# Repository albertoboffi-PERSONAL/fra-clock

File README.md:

# fra-clock

A one-off gift PCB designed in **KiCad 10**: an ESP32 clock with a ring of 180 WS2812B‑2020 LEDs, a photo printed in exposed copper on the front, two Makerverse 8 Ω / 5 W speakers driven by two MAX98357A I²S amplifiers, USB‑C power/programming (CH340C) and an NFC tag area.

| | |
|---|---|
| Board | 2 layers, 210 × 297 mm (A4), R3 corners |
| MCU | ESP32‑WROOM‑32E |
| LEDs | 180 × WS2812B‑2020 (4 chains, 74AHCT125 level shifter) |
| Audio | 2 × MAX98357A → 2 × JST PH (speakers Core Electronics CE08483) |
| Power / USB | USB‑C (HRO TYPE‑C‑31‑M‑12), 2 A PTC, AP2112K‑3.3, USBLC6‑2SC6, CH340C |
| Status | Routed, DRC clean (0 errors, 0 unconnected), Gerber/drill + JLCPCB BOM/CPL generated. **Not fabricated yet.** |

## Repository layout

```
hardware/                 KiCad project – open hardware/fra_clock.kicad_pro
  fra_clock.kicad_pcb     board
  fra_clock.kicad_sch     root schematic (+ led_ring.kicad_sch sub-sheet)
  fra_clock.pretty/       project footprints (photo art ART_FOTO, speaker outline)
  3d/                     project 3D models (speaker, LCSC/EasyEDA models in lcsc/)
production/
  fra_clock_gerber_jlcpcb.zip   upload this to the fab
  gerber/                 Gerber X2 + Excellon drill (+ drill maps)
  assembly/               JLCPCB BOM and CPL (pick & place)
  preview/                Gerber renders used for the visual check
docs/
  routing-report.md       full design/routing report (Italian)
  checks/                 DRC and verification outputs referenced by the report
  images/                 3D renders
art/
  source/foto.jpeg        original photo
  generated/              dithered bitmap, rectangle list, previews
scripts/                  automation used to build the board (see scripts/README.md)
```

## Ordering (JLCPCB)

1. Upload `production/fra_clock_gerber_jlcpcb.zip` (2 layers, 1.6 mm).
2. Surface finish: **ENIG** keeps the copper photo gold and flat (HASL turns it silver and uneven). Solder-mask colour sets the photo contrast.
3. For assembly upload `production/assembly/fra_clock_BOM_JLCPCB.csv` and `fra_clock_CPL_JLCPCB.csv`, then check rotation / pin 1 in the placement preview (SOT‑23/‑5/‑6, SOIC, TQFN, WS2812B‑2020, ESP32 antenna towards the edge, USB‑C, JST, C69 polarity).
4. Open decisions before ordering: ESP32 flash size (BOM uses N4 = C701341; N8 = C701342, N16 = C701343); stock and prices were not checked.

The NFC tag (NTAG216 sticker) has no footprint and is applied by hand in the keep-out area.

## Regenerating the production files

From the repository root, with KiCad 10 (`kicad-cli`):

```sh
KC=/Applications/KiCad/KiCad.app/Contents/MacOS/kicad-cli
$KC pcb drc --refill-zones --schematic-parity --format json --severity-all -o docs/checks/drc_latest.json hardware/fra_clock.kicad_pcb
$KC pcb export gerbers -o production/gerber/ --layers F.Cu,B.Cu,F.Paste,B.Paste,F.Silkscreen,B.Silkscreen,F.Mask,B.Mask,Edge.Cuts --subtract-soldermask --check-zones hardware/fra_clock.kicad_pcb
$KC pcb export drill -o production/gerber/ --format excellon --drill-origin absolute --excellon-units mm --excellon-zeros-format decimal --excellon-oval-format alternate --excellon-separate-th --generate-map --map-format gerberx2 hardware/fra_clock.kicad_pcb
python3 scripts/production/dump_fps.py hardware/fra_clock.kicad_pcb /tmp/fps.json
(cd production/assembly && python3 ../../scripts/production/make_bom_cpl.py /tmp/fps.json)
```

## Known open points

See `docs/routing-report.md` §5: a ~1035 mm² island of the bottom GND pour around U6/C4 is tied to GND only through top-side bridges; the exposed-pad vias of U101/U102 are not plugged; the `Power` net class is not assigned (widths are set explicitly on the tracks).

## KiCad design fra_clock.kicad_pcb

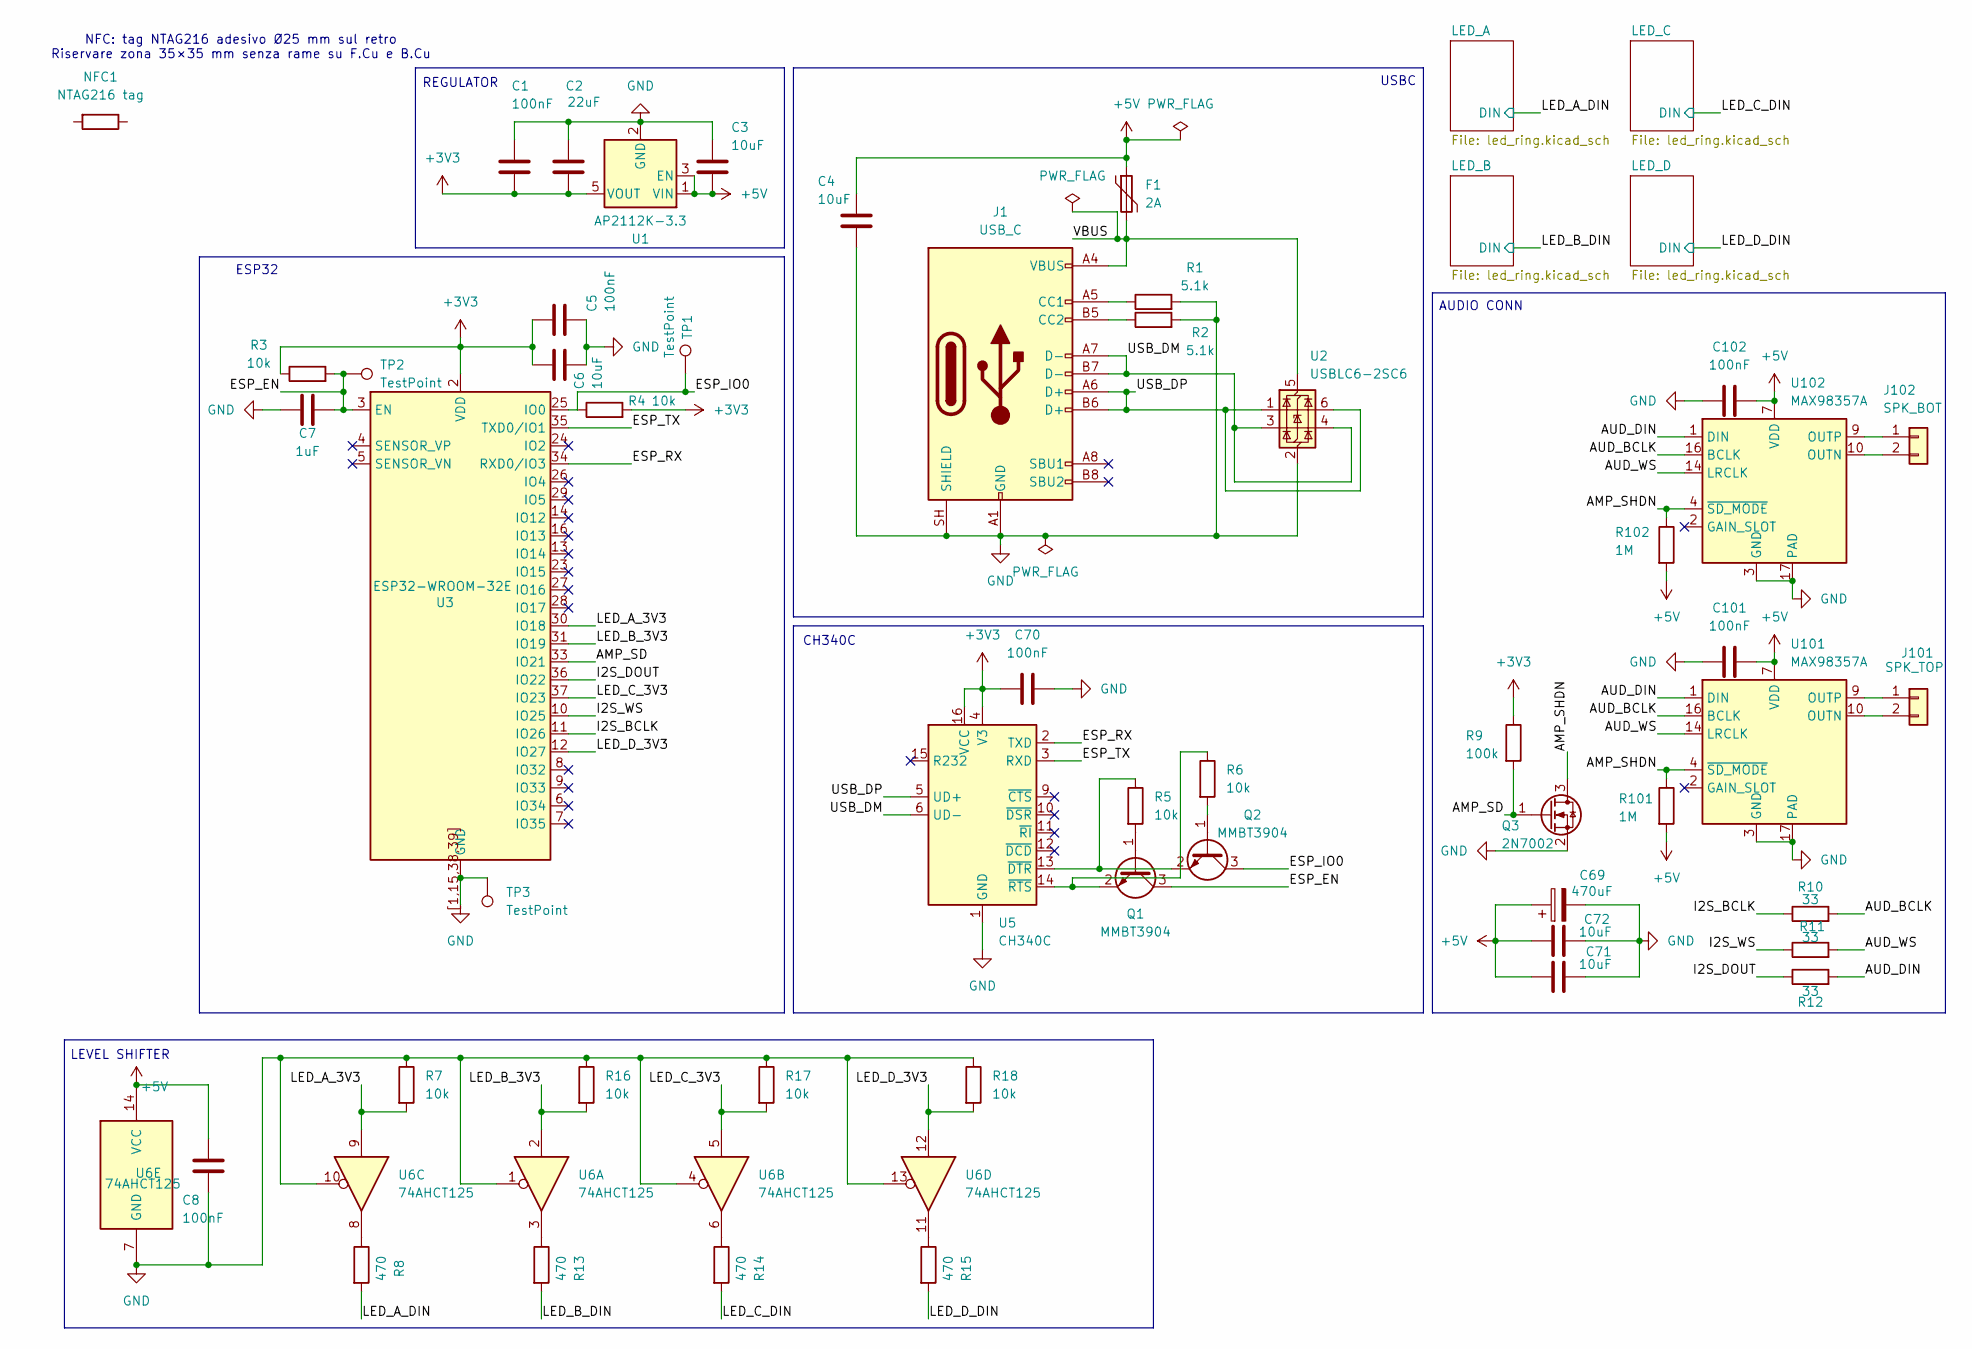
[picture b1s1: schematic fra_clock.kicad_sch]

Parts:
C1, C5, C8, C70: 100nF; C_0603_1608Metric
C2: 22uF; C_0805_2012Metric
C3, C4, C6, C71, C72: 10uF; C_0805_2012Metric
C7: 1uF; C_0603_1608Metric
C69: 470uF; CP_Elec_8x10
C101, C102: 100nF; C_0402_1005Metric
F1: 2A; Fuse_1812_4532Metric
J1: USB_C; USB_C_Receptacle_HRO_TYPE-C-31-M-12
J101: SPK_TOP; JST_PH_S2B-PH-SM4-TB_1x02-1MP_P2.00mm_Horizontal
J102: SPK_BOT; JST_PH_S2B-PH-SM4-TB_1x02-1MP_P2.00mm_Horizontal
NFC1: NTAG216 tag
Q1, Q2: MMBT3904; SOT-23
Q3: 2N7002; SOT-23
R1, R2: 5.1k; R_0603_1608Metric
R3, R4, R5, R6, R7, R16, R17, R18: 10k; R_0603_1608Metric
R8, R13, R14, R15: 470; R_0603_1608Metric
R9: 100k; R_0603_1608Metric
R10, R11, R12: 33; R_0603_1608Metric
R101, R102: 1M; R_0603_1608Metric
TP1, TP2, TP3: TestPoint; TestPoint_Pad_D1.5mm
U1: AP2112K-3.3; SOT-23-5
U2: USBLC6-2SC6; SOT-23-6
U3: ESP32-WROOM-32E
U5: CH340C; SOIC-16_3.9x9.9mm_P1.27mm
U6: 74AHCT125; SOIC-14_3.9x8.7mm_P1.27mm
U101, U102: MAX98357A; TQFN-16-1EP_3x3mm_P0.5mm_EP1.23x1.23mm

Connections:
+3V3: C1.2, C2.2, C5.1, C6.1, C70.1, R3.1, R4.2, R9.1, U1.5 (VOUT), U3.2 (VDD), U5.4 (V3), U5.16 (VCC)
+5V: C3.2, C4.1, C8.1, C69.1, C71.1, C72.1, C101.1, C102.1, F1.1, R101.2, R102.2, U1.1 (VIN), U1.3 (EN), U6.14 (VCC), U101.7 (VDD), U101.8 (VDD), U102.7 (VDD), U102.8 (VDD); also elsewhere on the board
/AMP_SD: Q3.1 (G), R9.2, U3.33 (IO21)
/AMP_SHDN: Q3.3 (D), R101.1, R102.1, U101.4 (~SD_MODE), U102.4 (~SD_MODE)
/AUD_BCLK: R10.2, U101.16 (BCLK), U102.16 (BCLK)
/AUD_DIN: R12.2, U101.1 (DIN), U102.1 (DIN)
/AUD_WS: R11.2, U101.14 (LRCLK), U102.14 (LRCLK)
/ESP_EN: C7.1, Q1.3 (C), R3.2, TP2.1 (1_1), U3.3 (EN)
/ESP_IO0: Q2.3 (C), R4.1, TP1.1 (1_1), U3.25 (IO0)
/ESP_RX: U3.34 (RXD0/IO3), U5.2 (TXD)
/ESP_TX: U3.35 (TXD0/IO1), U5.3 (RXD)
/I2S_BCLK: R10.1, U3.11 (IO26)
/I2S_DOUT: R12.1, U3.36 (IO22)
/I2S_WS: R11.1, U3.10 (IO25)
/LED_A_3V3: R7.2, U3.30 (IO18), U6.9
/LED_A_DIN: R8.2; also elsewhere on the board
/LED_B_3V3: R16.2, U3.31 (IO19), U6.2
/LED_B_DIN: R13.2; also elsewhere on the board
/LED_C_3V3: R17.2, U3.37 (IO23), U6.5
/LED_C_DIN: R14.2; also elsewhere on the board
/LED_D_3V3: R18.2, U3.12 (IO27), U6.12
/LED_D_DIN: R15.2; also elsewhere on the board
/USB_DM: J1.A7 (D-), J1.B7 (D-), U2.3 (I/O2), U2.4 (I/O2), U5.6 (UD-)
/USB_DP: J1.A6 (D+), J1.B6 (D+), U2.1 (I/O1), U2.6 (I/O1), U5.5 (UD+)
/VBUS: F1.2, J1.A4 (VBUS), J1.A9 (VBUS), J1.B4 (VBUS), J1.B9 (VBUS), U2.5 (VBUS)
GND: C1.1, C2.1, C3.1, C4.2, C5.2, C6.2, C7.2, C8.2, C69.2, C70.2, C71.2, C72.2, C101.2, C102.2, J1.A1 (GND), J1.A12 (GND), J1.B1 (GND), J1.B12 (GND), J1.SH (SHIELD), Q3.2 (S), R1.2, R2.2, R7.1, R16.1, R17.1, R18.1, TP3.1 (1_1), U1.2 (GND), U2.2 (GND), U3.1 (GND), U3.15 (GND), U3.38 (GND), U3.39 (GND), U3.[1,15,38,39] (GND), U5.1 (GND), U6.1, U6.4, U6.7 (GND), U6.10, U6.13, U101.3 (GND), U101.11 (GND), U101.15 (GND), U101.17 (PAD), U102.3 (GND), U102.11 (GND), U102.15 (GND), U102.17 (PAD); also elsewhere on the board
unnamed: J1.A5 (CC1), R1.1
unnamed: J1.B5 (CC2), R2.1
unnamed: J101.1, U101.9 (OUTP)
unnamed: J101.2, U101.10 (OUTN)
unnamed: J102.1, U102.9 (OUTP)
unnamed: J102.2, U102.10 (OUTN)
unnamed: Q1.1 (B), R5.2
unnamed: Q1.2 (E), R6.1, U5.14 (~RTS)
unnamed: Q2.1 (B), R6.2
unnamed: Q2.2 (E), R5.1, U5.13 (~DTR)
unnamed: R8.1, U6.8
unnamed: R13.1, U6.3
unnamed: R14.1, U6.6
unnamed: R15.1, U6.11

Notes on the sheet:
CH340C
USBC
LEVEL SHIFTER
NFC: tag NTAG216 adesivo Ø25 mm sul retro Riservare zona 35×35 mm senza rame su F.Cu e B.Cu
AUDIO CONN
REGULATOR
ESP32

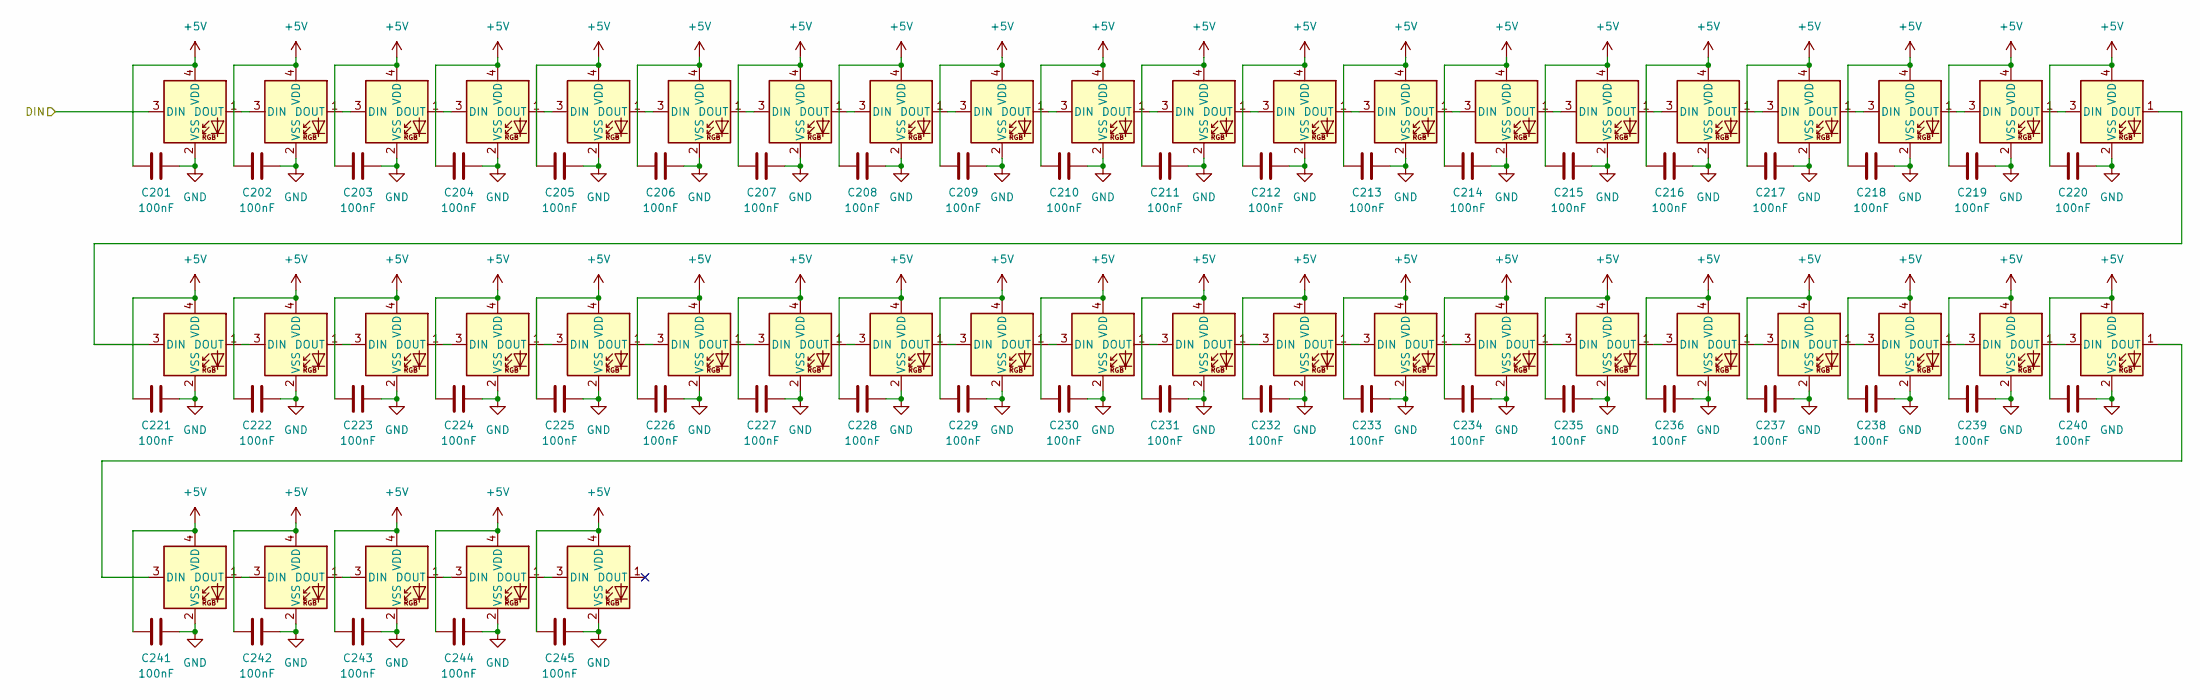
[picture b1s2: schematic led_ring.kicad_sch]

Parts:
C201, C202, C203, C204, C205, C206, C207, C208, C209, C210, C211, C212, C213, C214, C215, C216, C217, C218, C219, C220, C221, C222, C223, C224, C225, C226, C227, C228, C229, C230, C231, C232, C233, C234, C235, C236, C237, C238, C239, C240, C241, C242, C243, C244, C245: 100nF; C_0402_1005Metric
D201, D202, D203, D204, D205, D206, D207, D208, D209, D210, D211, D212, D213, D214, D215, D216, D217, D218, D219, D220, D221, D222, D223, D224, D225, D226, D227, D228, D229, D230, D231, D232, D233, D234, D235, D236, D237, D238, D239, D240, D241, D242, D243, D244, D245: WS2812B-2020; LED_WS2812B-2020_PLCC4_2.0x2.0mm

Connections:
+5V: C201.2, C202.2, C203.2, C204.2, C205.2, C206.2, C207.2, C208.2, C209.2, C210.2, C211.2, C212.2, C213.2, C214.2, C215.2, C216.2, C217.2, C218.2, C219.2, C220.2, C221.2, C222.2, C223.2, C224.2, C225.2, C226.2, C227.2, C228.2, C229.2, C230.2, C231.2, C232.2, C233.2, C234.2, C235.2, C236.2, C237.2, C238.2, C239.2, C240.2, C241.2, C242.2, C243.2, C244.2, C245.2, D201.4 (VDD), D202.4 (VDD), D203.4 (VDD), D204.4 (VDD), D205.4 (VDD), D206.4 (VDD), D207.4 (VDD), D208.4 (VDD), D209.4 (VDD), D210.4 (VDD), D211.4 (VDD), D212.4 (VDD), D213.4 (VDD), D214.4 (VDD), D215.4 (VDD), D216.4 (VDD), D217.4 (VDD), D218.4 (VDD), D219.4 (VDD), D220.4 (VDD), D221.4 (VDD), D222.4 (VDD), D223.4 (VDD), D224.4 (VDD), D225.4 (VDD), D226.4 (VDD), D227.4 (VDD), D228.4 (VDD), D229.4 (VDD), D230.4 (VDD), D231.4 (VDD), D232.4 (VDD), D233.4 (VDD), D234.4 (VDD), D235.4 (VDD), D236.4 (VDD), D237.4 (VDD), D238.4 (VDD), D239.4 (VDD), D240.4 (VDD), D241.4 (VDD), D242.4 (VDD), D243.4 (VDD), D244.4 (VDD), D245.4 (VDD); also elsewhere on the board
/LED_A_DIN: D201.3 (DIN); also elsewhere on the board
GND: C201.1, C202.1, C203.1, C204.1, C205.1, C206.1, C207.1, C208.1, C209.1, C210.1, C211.1, C212.1, C213.1, C214.1, C215.1, C216.1, C217.1, C218.1, C219.1, C220.1, C221.1, C222.1, C223.1, C224.1, C225.1, C226.1, C227.1, C228.1, C229.1, C230.1, C231.1, C232.1, C233.1, C234.1, C235.1, C236.1, C237.1, C238.1, C239.1, C240.1, C241.1, C242.1, C243.1, C244.1, C245.1, D201.2 (VSS), D202.2 (VSS), D203.2 (VSS), D204.2 (VSS), D205.2 (VSS), D206.2 (VSS), D207.2 (VSS), D208.2 (VSS), D209.2 (VSS), D210.2 (VSS), D211.2 (VSS), D212.2 (VSS), D213.2 (VSS), D214.2 (VSS), D215.2 (VSS), D216.2 (VSS), D217.2 (VSS), D218.2 (VSS), D219.2 (VSS), D220.2 (VSS), D221.2 (VSS), D222.2 (VSS), D223.2 (VSS), D224.2 (VSS), D225.2 (VSS), D226.2 (VSS), D227.2 (VSS), D228.2 (VSS), D229.2 (VSS), D230.2 (VSS), D231.2 (VSS), D232.2 (VSS), D233.2 (VSS), D234.2 (VSS), D235.2 (VSS), D236.2 (VSS), D237.2 (VSS), D238.2 (VSS), D239.2 (VSS), D240.2 (VSS), D241.2 (VSS), D242.2 (VSS), D243.2 (VSS), D244.2 (VSS), D245.2 (VSS); also elsewhere on the board
unnamed: D201.1 (DOUT), D202.3 (DIN)
unnamed: D202.1 (DOUT), D203.3 (DIN)
unnamed: D203.1 (DOUT), D204.3 (DIN)
unnamed: D204.1 (DOUT), D205.3 (DIN)
unnamed: D205.1 (DOUT), D206.3 (DIN)
unnamed: D206.1 (DOUT), D207.3 (DIN)
unnamed: D207.1 (DOUT), D208.3 (DIN)
unnamed: D208.1 (DOUT), D209.3 (DIN)
unnamed: D209.1 (DOUT), D210.3 (DIN)
unnamed: D210.1 (DOUT), D211.3 (DIN)
unnamed: D211.1 (DOUT), D212.3 (DIN)
unnamed: D212.1 (DOUT), D213.3 (DIN)
unnamed: D213.1 (DOUT), D214.3 (DIN)
unnamed: D214.1 (DOUT), D215.3 (DIN)
unnamed: D215.1 (DOUT), D216.3 (DIN)
unnamed: D216.1 (DOUT), D217.3 (DIN)
unnamed: D217.1 (DOUT), D218.3 (DIN)
unnamed: D218.1 (DOUT), D219.3 (DIN)
unnamed: D219.1 (DOUT), D220.3 (DIN)
unnamed: D220.1 (DOUT), D221.3 (DIN)
unnamed: D221.1 (DOUT), D222.3 (DIN)
unnamed: D222.1 (DOUT), D223.3 (DIN)
unnamed: D223.1 (DOUT), D224.3 (DIN)
unnamed: D224.1 (DOUT), D225.3 (DIN)
unnamed: D225.1 (DOUT), D226.3 (DIN)
unnamed: D226.1 (DOUT), D227.3 (DIN)
unnamed: D227.1 (DOUT), D228.3 (DIN)
unnamed: D228.1 (DOUT), D229.3 (DIN)
unnamed: D229.1 (DOUT), D230.3 (DIN)
unnamed: D230.1 (DOUT), D231.3 (DIN)
unnamed: D231.1 (DOUT), D232.3 (DIN)
unnamed: D232.1 (DOUT), D233.3 (DIN)
unnamed: D233.1 (DOUT), D234.3 (DIN)
unnamed: D234.1 (DOUT), D235.3 (DIN)
unnamed: D235.1 (DOUT), D236.3 (DIN)
unnamed: D236.1 (DOUT), D237.3 (DIN)
unnamed: D237.1 (DOUT), D238.3 (DIN)
unnamed: D238.1 (DOUT), D239.3 (DIN)
unnamed: D239.1 (DOUT), D240.3 (DIN)
unnamed: D240.1 (DOUT), D241.3 (DIN)
unnamed: D241.1 (DOUT), D242.3 (DIN)
unnamed: D242.1 (DOUT), D243.3 (DIN)
unnamed: D243.1 (DOUT), D244.3 (DIN)
unnamed: D244.1 (DOUT), D245.3 (DIN)

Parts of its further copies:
C301, C302, C303, C304, C305, C306, C307, C308, C309, C310, C311, C312, C313, C314, C315, C316, C317, C318, C319, C320, C321, C322, C323, C324, C325, C326, C327, C328, C329, C330, C331, C332, C333, C334, C335, C336, C337, C338, C339, C340, C341, C342, C343, C344, C345, C401, C402, C403, C404, C405, C406, C407, C408, C409, C410, C411, C412, C413, C414, C415, C416, C417, C418, C419, C420, C421, C422, C423, C424, C425, C426, C427, C428, C429, C430, C431, C432, C433, C434, C435, C436, C437, C438, C439, C440, C441, C442, C443, C444, C445, C501, C502, C503, C504, C505, C506, C507, C508, C509, C510, C511, C512, C513, C514, C515, C516, C517, C518, C519, C520, C521, C522, C523, C524, C525, C526, C527, C528, C529, C530, C531, C532, C533, C534, C535, C536, C537, C538, C539, C540, C541, C542, C543, C544, C545: 100nF; C_0402_1005Metric
D301, D302, D303, D304, D305, D306, D307, D308, D309, D310, D311, D312, D313, D314, D315, D316, D317, D318, D319, D320, D321, D322, D323, D324, D325, D326, D327, D328, D329, D330, D331, D332, D333, D334, D335, D336, D337, D338, D339, D340, D341, D342, D343, D344, D345, D401, D402, D403, D404, D405, D406, D407, D408, D409, D410, D411, D412, D413, D414, D415, D416, D417, D418, D419, D420, D421, D422, D423, D424, D425, D426, D427, D428, D429, D430, D431, D432, D433, D434, D435, D436, D437, D438, D439, D440, D441, D442, D443, D444, D445, D501, D502, D503, D504, D505, D506, D507, D508, D509, D510, D511, D512, D513, D514, D515, D516, D517, D518, D519, D520, D521, D522, D523, D524, D525, D526, D527, D528, D529, D530, D531, D532, D533, D534, D535, D536, D537, D538, D539, D540, D541, D542, D543, D544, D545: WS2812B-2020; LED_WS2812B-2020_PLCC4_2.0x2.0mm

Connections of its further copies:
+5V: C301.2, C302.2, C303.2, C304.2, C305.2, C306.2, C307.2, C308.2, C309.2, C310.2, C311.2, C312.2, C313.2, C314.2, C315.2, C316.2, C317.2, C318.2, C319.2, C320.2, C321.2, C322.2, C323.2, C324.2, C325.2, C326.2, C327.2, C328.2, C329.2, C330.2, C331.2, C332.2, C333.2, C334.2, C335.2, C336.2, C337.2, C338.2, C339.2, C340.2, C341.2, C342.2, C343.2, C344.2, C345.2, C401.2, C402.2, C403.2, C404.2, C405.2, C406.2, C407.2, C408.2, C409.2, C410.2, C411.2, C412.2, C413.2, C414.2, C415.2, C416.2, C417.2, C418.2, C419.2, C420.2, C421.2, C422.2, C423.2, C424.2, C425.2, C426.2, C427.2, C428.2, C429.2, C430.2, C431.2, C432.2, C433.2, C434.2, C435.2, C436.2, C437.2, C438.2, C439.2, C440.2, C441.2, C442.2, C443.2, C444.2, C445.2, C501.2, C502.2, C503.2, C504.2, C505.2, C506.2, C507.2, C508.2, C509.2, C510.2, C511.2, C512.2, C513.2, C514.2, C515.2, C516.2, C517.2, C518.2, C519.2, C520.2, C521.2, C522.2, C523.2, C524.2, C525.2, C526.2, C527.2, C528.2, C529.2, C530.2, C531.2, C532.2, C533.2, C534.2, C535.2, C536.2, C537.2, C538.2, C539.2, C540.2, C541.2, C542.2, C543.2, C544.2, C545.2, D301.4 (VDD), D302.4 (VDD), D303.4 (VDD), D304.4 (VDD), D305.4 (VDD), D306.4 (VDD), D307.4 (VDD), D308.4 (VDD), D309.4 (VDD), D310.4 (VDD), D311.4 (VDD), D312.4 (VDD), D313.4 (VDD), D314.4 (VDD), D315.4 (VDD), D316.4 (VDD), D317.4 (VDD), D318.4 (VDD), D319.4 (VDD), D320.4 (VDD), D321.4 (VDD), D322.4 (VDD), D323.4 (VDD), D324.4 (VDD), D325.4 (VDD), D326.4 (VDD), D327.4 (VDD), D328.4 (VDD), D329.4 (VDD), D330.4 (VDD), D331.4 (VDD), D332.4 (VDD), D333.4 (VDD), D334.4 (VDD), D335.4 (VDD), D336.4 (VDD), D337.4 (VDD), D338.4 (VDD), D339.4 (VDD), D340.4 (VDD), D341.4 (VDD), D342.4 (VDD), D343.4 (VDD), D344.4 (VDD), D345.4 (VDD), D401.4 (VDD), D402.4 (VDD), D403.4 (VDD), D404.4 (VDD), D405.4 (VDD), D406.4 (VDD), D407.4 (VDD), D408.4 (VDD), D409.4 (VDD), D410.4 (VDD), D411.4 (VDD), D412.4 (VDD), D413.4 (VDD), D414.4 (VDD), D415.4 (VDD), D416.4 (VDD), D417.4 (VDD), D418.4 (VDD), D419.4 (VDD), D420.4 (VDD), D421.4 (VDD), D422.4 (VDD), D423.4 (VDD), D424.4 (VDD), D425.4 (VDD), D426.4 (VDD), D427.4 (VDD), D428.4 (VDD), D429.4 (VDD), D430.4 (VDD), D431.4 (VDD), D432.4 (VDD), D433.4 (VDD), D434.4 (VDD), D435.4 (VDD), D436.4 (VDD), D437.4 (VDD), D438.4 (VDD), D439.4 (VDD), D440.4 (VDD), D441.4 (VDD), D442.4 (VDD), D443.4 (VDD), D444.4 (VDD), D445.4 (VDD), D501.4 (VDD), D502.4 (VDD), D503.4 (VDD), D504.4 (VDD), D505.4 (VDD), D506.4 (VDD), D507.4 (VDD), D508.4 (VDD), D509.4 (VDD), D510.4 (VDD), D511.4 (VDD), D512.4 (VDD), D513.4 (VDD), D514.4 (VDD), D515.4 (VDD), D516.4 (VDD), D517.4 (VDD), D518.4 (VDD), D519.4 (VDD), D520.4 (VDD), D521.4 (VDD), D522.4 (VDD), D523.4 (VDD), D524.4 (VDD), D525.4 (VDD), D526.4 (VDD), D527.4 (VDD), D528.4 (VDD), D529.4 (VDD), D530.4 (VDD), D531.4 (VDD), D532.4 (VDD), D533.4 (VDD), D534.4 (VDD), D535.4 (VDD), D536.4 (VDD), D537.4 (VDD), D538.4 (VDD), D539.4 (VDD), D540.4 (VDD), D541.4 (VDD), D542.4 (VDD), D543.4 (VDD), D544.4 (VDD), D545.4 (VDD); also elsewhere on the board
/LED_B_DIN: D301.3 (DIN); also elsewhere on the board
/LED_C_DIN: D401.3 (DIN); also elsewhere on the board
/LED_D_DIN: D501.3 (DIN); also elsewhere on the board
GND: C301.1, C302.1, C303.1, C304.1, C305.1, C306.1, C307.1, C308.1, C309.1, C310.1, C311.1, C312.1, C313.1, C314.1, C315.1, C316.1, C317.1, C318.1, C319.1, C320.1, C321.1, C322.1, C323.1, C324.1, C325.1, C326.1, C327.1, C328.1, C329.1, C330.1, C331.1, C332.1, C333.1, C334.1, C335.1, C336.1, C337.1, C338.1, C339.1, C340.1, C341.1, C342.1, C343.1, C344.1, C345.1, C401.1, C402.1, C403.1, C404.1, C405.1, C406.1, C407.1, C408.1, C409.1, C410.1, C411.1, C412.1, C413.1, C414.1, C415.1, C416.1, C417.1, C418.1, C419.1, C420.1, C421.1, C422.1, C423.1, C424.1, C425.1, C426.1, C427.1, C428.1, C429.1, C430.1, C431.1, C432.1, C433.1, C434.1, C435.1, C436.1, C437.1, C438.1, C439.1, C440.1, C441.1, C442.1, C443.1, C444.1, C445.1, C501.1, C502.1, C503.1, C504.1, C505.1, C506.1, C507.1, C508.1, C509.1, C510.1, C511.1, C512.1, C513.1, C514.1, C515.1, C516.1, C517.1, C518.1, C519.1, C520.1, C521.1, C522.1, C523.1, C524.1, C525.1, C526.1, C527.1, C528.1, C529.1, C530.1, C531.1, C532.1, C533.1, C534.1, C535.1, C536.1, C537.1, C538.1, C539.1, C540.1, C541.1, C542.1, C543.1, C544.1, C545.1, D301.2 (VSS), D302.2 (VSS), D303.2 (VSS), D304.2 (VSS), D305.2 (VSS), D306.2 (VSS), D307.2 (VSS), D308.2 (VSS), D309.2 (VSS), D310.2 (VSS), D311.2 (VSS), D312.2 (VSS), D313.2 (VSS), D314.2 (VSS), D315.2 (VSS), D316.2 (VSS), D317.2 (VSS), D318.2 (VSS), D319.2 (VSS), D320.2 (VSS), D321.2 (VSS), D322.2 (VSS), D323.2 (VSS), D324.2 (VSS), D325.2 (VSS), D326.2 (VSS), D327.2 (VSS), D328.2 (VSS), D329.2 (VSS), D330.2 (VSS), D331.2 (VSS), D332.2 (VSS), D333.2 (VSS), D334.2 (VSS), D335.2 (VSS), D336.2 (VSS), D337.2 (VSS), D338.2 (VSS), D339.2 (VSS), D340.2 (VSS), D341.2 (VSS), D342.2 (VSS), D343.2 (VSS), D344.2 (VSS), D345.2 (VSS), D401.2 (VSS), D402.2 (VSS), D403.2 (VSS), D404.2 (VSS), D405.2 (VSS), D406.2 (VSS), D407.2 (VSS), D408.2 (VSS), D409.2 (VSS), D410.2 (VSS), D411.2 (VSS), D412.2 (VSS), D413.2 (VSS), D414.2 (VSS), D415.2 (VSS), D416.2 (VSS), D417.2 (VSS), D418.2 (VSS), D419.2 (VSS), D420.2 (VSS), D421.2 (VSS), D422.2 (VSS), D423.2 (VSS), D424.2 (VSS), D425.2 (VSS), D426.2 (VSS), D427.2 (VSS), D428.2 (VSS), D429.2 (VSS), D430.2 (VSS), D431.2 (VSS), D432.2 (VSS), D433.2 (VSS), D434.2 (VSS), D435.2 (VSS), D436.2 (VSS), D437.2 (VSS), D438.2 (VSS), D439.2 (VSS), D440.2 (VSS), D441.2 (VSS), D442.2 (VSS), D443.2 (VSS), D444.2 (VSS), D445.2 (VSS), D501.2 (VSS), D502.2 (VSS), D503.2 (VSS), D504.2 (VSS), D505.2 (VSS), D506.2 (VSS), D507.2 (VSS), D508.2 (VSS), D509.2 (VSS), D510.2 (VSS), D511.2 (VSS), D512.2 (VSS), D513.2 (VSS), D514.2 (VSS), D515.2 (VSS), D516.2 (VSS), D517.2 (VSS), D518.2 (VSS), D519.2 (VSS), D520.2 (VSS), D521.2 (VSS), D522.2 (VSS), D523.2 (VSS), D524.2 (VSS), D525.2 (VSS), D526.2 (VSS), D527.2 (VSS), D528.2 (VSS), D529.2 (VSS), D530.2 (VSS), D531.2 (VSS), D532.2 (VSS), D533.2 (VSS), D534.2 (VSS), D535.2 (VSS), D536.2 (VSS), D537.2 (VSS), D538.2 (VSS), D539.2 (VSS), D540.2 (VSS), D541.2 (VSS), D542.2 (VSS), D543.2 (VSS), D544.2 (VSS), D545.2 (VSS); also elsewhere on the board
unnamed: D301.1 (DOUT), D302.3 (DIN)
unnamed: D302.1 (DOUT), D303.3 (DIN)
unnamed: D303.1 (DOUT), D304.3 (DIN)
unnamed: D304.1 (DOUT), D305.3 (DIN)
unnamed: D305.1 (DOUT), D306.3 (DIN)
unnamed: D306.1 (DOUT), D307.3 (DIN)
unnamed: D307.1 (DOUT), D308.3 (DIN)
unnamed: D308.1 (DOUT), D309.3 (DIN)
unnamed: D309.1 (DOUT), D310.3 (DIN)
unnamed: D310.1 (DOUT), D311.3 (DIN)
unnamed: D311.1 (DOUT), D312.3 (DIN)
unnamed: D312.1 (DOUT), D313.3 (DIN)
unnamed: D313.1 (DOUT), D314.3 (DIN)
unnamed: D314.1 (DOUT), D315.3 (DIN)
unnamed: D315.1 (DOUT), D316.3 (DIN)
unnamed: D316.1 (DOUT), D317.3 (DIN)
unnamed: D317.1 (DOUT), D318.3 (DIN)
unnamed: D318.1 (DOUT), D319.3 (DIN)
unnamed: D319.1 (DOUT), D320.3 (DIN)
unnamed: D320.1 (DOUT), D321.3 (DIN)
unnamed: D321.1 (DOUT), D322.3 (DIN)
unnamed: D322.1 (DOUT), D323.3 (DIN)
unnamed: D323.1 (DOUT), D324.3 (DIN)
unnamed: D324.1 (DOUT), D325.3 (DIN)
unnamed: D325.1 (DOUT), D326.3 (DIN)
unnamed: D326.1 (DOUT), D327.3 (DIN)
unnamed: D327.1 (DOUT), D328.3 (DIN)
unnamed: D328.1 (DOUT), D329.3 (DIN)
unnamed: D329.1 (DOUT), D330.3 (DIN)
unnamed: D330.1 (DOUT), D331.3 (DIN)
unnamed: D331.1 (DOUT), D332.3 (DIN)
unnamed: D332.1 (DOUT), D333.3 (DIN)
unnamed: D333.1 (DOUT), D334.3 (DIN)
unnamed: D334.1 (DOUT), D335.3 (DIN)
unnamed: D335.1 (DOUT), D336.3 (DIN)
unnamed: D336.1 (DOUT), D337.3 (DIN)
unnamed: D337.1 (DOUT), D338.3 (DIN)
unnamed: D338.1 (DOUT), D339.3 (DIN)
unnamed: D339.1 (DOUT), D340.3 (DIN)
unnamed: D340.1 (DOUT), D341.3 (DIN)
unnamed: D341.1 (DOUT), D342.3 (DIN)
unnamed: D342.1 (DOUT), D343.3 (DIN)
unnamed: D343.1 (DOUT), D344.3 (DIN)
unnamed: D344.1 (DOUT), D345.3 (DIN)
unnamed: D401.1 (DOUT), D402.3 (DIN)
unnamed: D402.1 (DOUT), D403.3 (DIN)
unnamed: D403.1 (DOUT), D404.3 (DIN)
unnamed: D404.1 (DOUT), D405.3 (DIN)
unnamed: D405.1 (DOUT), D406.3 (DIN)
unnamed: D406.1 (DOUT), D407.3 (DIN)
unnamed: D407.1 (DOUT), D408.3 (DIN)
unnamed: D408.1 (DOUT), D409.3 (DIN)
unnamed: D409.1 (DOUT), D410.3 (DIN)
unnamed: D410.1 (DOUT), D411.3 (DIN)
unnamed: D411.1 (DOUT), D412.3 (DIN)
unnamed: D412.1 (DOUT), D413.3 (DIN)
unnamed: D413.1 (DOUT), D414.3 (DIN)
unnamed: D414.1 (DOUT), D415.3 (DIN)
unnamed: D415.1 (DOUT), D416.3 (DIN)
unnamed: D416.1 (DOUT), D417.3 (DIN)
unnamed: D417.1 (DOUT), D418.3 (DIN)
unnamed: D418.1 (DOUT), D419.3 (DIN)
unnamed: D419.1 (DOUT), D420.3 (DIN)
unnamed: D420.1 (DOUT), D421.3 (DIN)
unnamed: D421.1 (DOUT), D422.3 (DIN)
unnamed: D422.1 (DOUT), D423.3 (DIN)
unnamed: D423.1 (DOUT), D424.3 (DIN)
unnamed: D424.1 (DOUT), D425.3 (DIN)
unnamed: D425.1 (DOUT), D426.3 (DIN)
unnamed: D426.1 (DOUT), D427.3 (DIN)
unnamed: D427.1 (DOUT), D428.3 (DIN)
unnamed: D428.1 (DOUT), D429.3 (DIN)
unnamed: D429.1 (DOUT), D430.3 (DIN)
unnamed: D430.1 (DOUT), D431.3 (DIN)
unnamed: D431.1 (DOUT), D432.3 (DIN)
unnamed: D432.1 (DOUT), D433.3 (DIN)
unnamed: D433.1 (DOUT), D434.3 (DIN)
unnamed: D434.1 (DOUT), D435.3 (DIN)
unnamed: D435.1 (DOUT), D436.3 (DIN)
unnamed: D436.1 (DOUT), D437.3 (DIN)
unnamed: D437.1 (DOUT), D438.3 (DIN)
unnamed: D438.1 (DOUT), D439.3 (DIN)
unnamed: D439.1 (DOUT), D440.3 (DIN)
unnamed: D440.1 (DOUT), D441.3 (DIN)
unnamed: D441.1 (DOUT), D442.3 (DIN)
unnamed: D442.1 (DOUT), D443.3 (DIN)
unnamed: D443.1 (DOUT), D444.3 (DIN)
unnamed: D444.1 (DOUT), D445.3 (DIN)
unnamed: D501.1 (DOUT), D502.3 (DIN)
unnamed: D502.1 (DOUT), D503.3 (DIN)
unnamed: D503.1 (DOUT), D504.3 (DIN)
unnamed: D504.1 (DOUT), D505.3 (DIN)
unnamed: D505.1 (DOUT), D506.3 (DIN)
unnamed: D506.1 (DOUT), D507.3 (DIN)
unnamed: D507.1 (DOUT), D508.3 (DIN)
unnamed: D508.1 (DOUT), D509.3 (DIN)
unnamed: D509.1 (DOUT), D510.3 (DIN)
unnamed: D510.1 (DOUT), D511.3 (DIN)
unnamed: D511.1 (DOUT), D512.3 (DIN)
unnamed: D512.1 (DOUT), D513.3 (DIN)
unnamed: D513.1 (DOUT), D514.3 (DIN)
unnamed: D514.1 (DOUT), D515.3 (DIN)
unnamed: D515.1 (DOUT), D516.3 (DIN)
unnamed: D516.1 (DOUT), D517.3 (DIN)
unnamed: D517.1 (DOUT), D518.3 (DIN)
unnamed: D518.1 (DOUT), D519.3 (DIN)
unnamed: D519.1 (DOUT), D520.3 (DIN)
unnamed: D520.1 (DOUT), D521.3 (DIN)
unnamed: D521.1 (DOUT), D522.3 (DIN)
unnamed: D522.1 (DOUT), D523.3 (DIN)
unnamed: D523.1 (DOUT), D524.3 (DIN)
unnamed: D524.1 (DOUT), D525.3 (DIN)
unnamed: D525.1 (DOUT), D526.3 (DIN)
unnamed: D526.1 (DOUT), D527.3 (DIN)
unnamed: D527.1 (DOUT), D528.3 (DIN)
unnamed: D528.1 (DOUT), D529.3 (DIN)
unnamed: D529.1 (DOUT), D530.3 (DIN)
unnamed: D530.1 (DOUT), D531.3 (DIN)
unnamed: D531.1 (DOUT), D532.3 (DIN)
unnamed: D532.1 (DOUT), D533.3 (DIN)
unnamed: D533.1 (DOUT), D534.3 (DIN)
unnamed: D534.1 (DOUT), D535.3 (DIN)
unnamed: D535.1 (DOUT), D536.3 (DIN)
unnamed: D536.1 (DOUT), D537.3 (DIN)
unnamed: D537.1 (DOUT), D538.3 (DIN)
unnamed: D538.1 (DOUT), D539.3 (DIN)
unnamed: D539.1 (DOUT), D540.3 (DIN)
unnamed: D540.1 (DOUT), D541.3 (DIN)
unnamed: D541.1 (DOUT), D542.3 (DIN)
unnamed: D542.1 (DOUT), D543.3 (DIN)
unnamed: D543.1 (DOUT), D544.3 (DIN)
unnamed: D544.1 (DOUT), D545.3 (DIN)

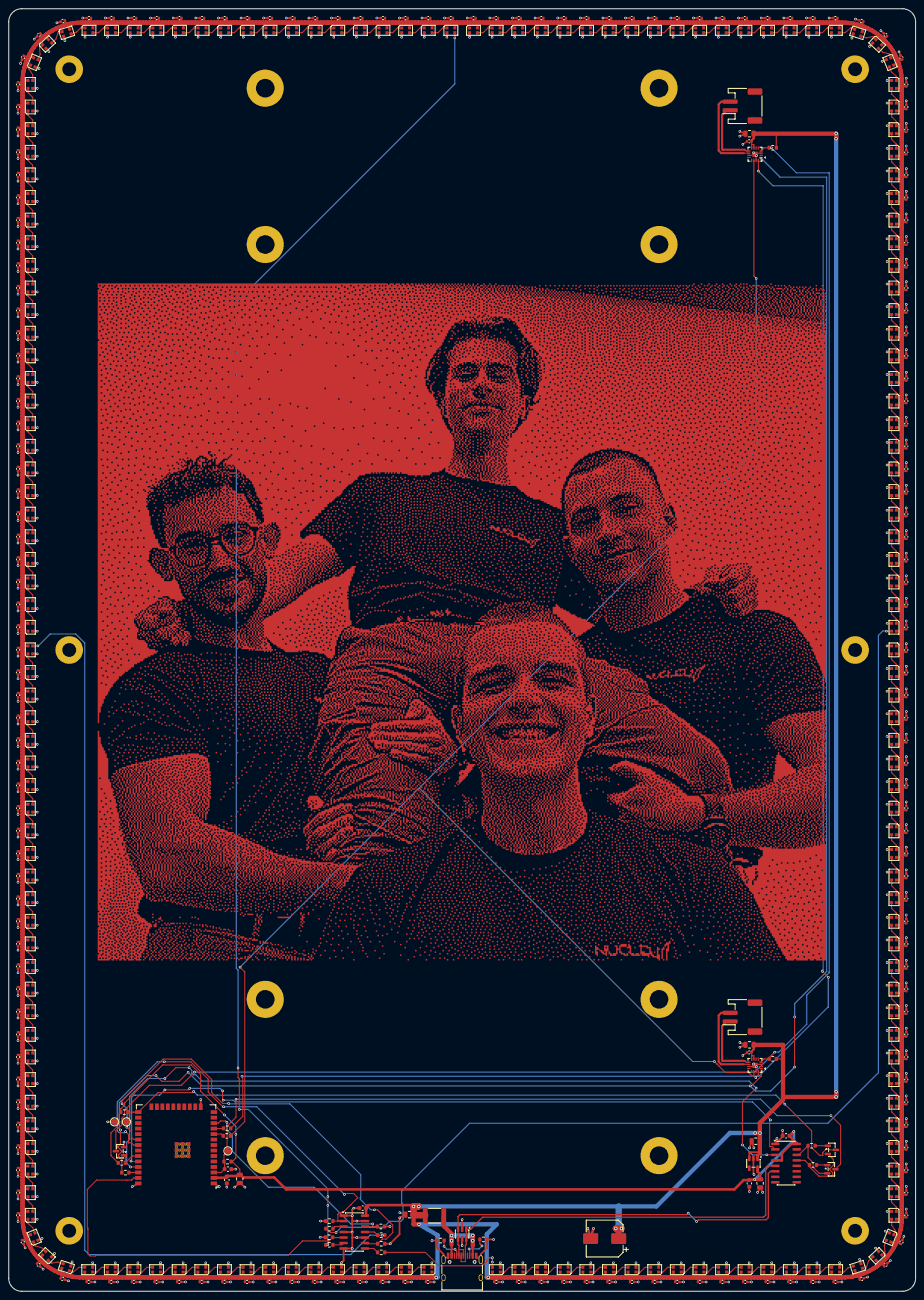
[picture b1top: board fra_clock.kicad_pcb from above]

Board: 2 copper layers, 210.0 x 297.0 mm, 428 parts (0 on the bottom side), 216 nets.

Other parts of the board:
ART1: ART_FOTO
H1, H2, H7, H8, H13, H14: MountingHole_3.2mm_M3_Pad
H3, H4, H5, H6, H9, H10, H11, H12: MountingHole_4.3mm_M4_Pad
LS1, LS2: CE08483; Speaker_Makerverse_CE08483_100x45

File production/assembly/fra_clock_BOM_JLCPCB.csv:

Comment,Designator,Footprint,LCSC Part #,Manufacturer Part,Quantity
100nF,"C1,C5,C8,C70",0603,C14663,CC0603KRX7R9BB104,4
22uF,C2,0805,C45783,CL21A226MAQNNNE,1
10uF,"C3,C4,C6,C71,C72",0805,C15850,CL21A106KAYNNNE,5
1uF,C7,0603,C15849,CL10A105KB8NNNC,1
470uF,C69,SMD D8xL10.2,C82006,RVT1C471M0810 (16V),1
100nF,"C101,C102,C201,C202,C203,C204,C205,C206,C207,C208,C209,C210,C211,C212,C213,C214,C215,C216,C217,C218,C219,C220,C221,C222,C223,C224,C225,C226,C227,C228,C229,C230,C231,C232,C233,C234,C235,C236,C237,C238,C239,C240,C241,C242,C243,C244,C245,C301,C302,C303,C304,C305,C306,C307,C308,C309,C310,C311,C312,C313,C314,C315,C316,C317,C318,C319,C320,C321,C322,C323,C324,C325,C326,C327,C328,C329,C330,C331,C332,C333,C334,C335,C336,C337,C338,C339,C340,C341,C342,C343,C344,C345,C401,C402,C403,C404,C405,C406,C407,C408,C409,C410,C411,C412,C413,C414,C415,C416,C417,C418,C419,C420,C421,C422,C423,C424,C425,C426,C427,C428,C429,C430,C431,C432,C433,C434,C435,C436,C437,C438,C439,C440,C441,C442,C443,C444,C445,C501,C502,C503,C504,C505,C506,C507,C508,C509,C510,C511,C512,C513,C514,C515,C516,C517,C518,C519,C520,C521,C522,C523,C524,C525,C526,C527,C528,C529,C530,C531,C532,C533,C534,C535,C536,C537,C538,C539,C540,C541,C542,C543,C544,C545",0402,C1525,CL05B104KO5NNNC,182
WS2812B-2020,"D201,D202,D203,D204,D205,D206,D207,D208,D209,D210,D211,D212,D213,D214,D215,D216,D217,D218,D219,D220,D221,D222,D223,D224,D225,D226,D227,D228,D229,D230,D231,D232,D233,D234,D235,D236,D237,D238,D239,D240,D241,D242,D243,D244,D245,D301,D302,D303,D304,D305,D306,D307,D308,D309,D310,D311,D312,D313,D314,D315,D316,D317,D318,D319,D320,D321,D322,D323,D324,D325,D326,D327,D328,D329,D330,D331,D332,D333,D334,D335,D336,D337,D338,D339,D340,D341,D342,D343,D344,D345,D401,D402,D403,D404,D405,D406,D407,D408,D409,D410,D411,D412,D413,D414,D415,D416,D417,D418,D419,D420,D421,D422,D423,D424,D425,D426,D427,D428,D429,D430,D431,D432,D433,D434,D435,D436,D437,D438,D439,D440,D441,D442,D443,D444,D445,D501,D502,D503,D504,D505,D506,D507,D508,D509,D510,D511,D512,D513,D514,D515,D516,D517,D518,D519,D520,D521,D522,D523,D524,D525,D526,D527,D528,D529,D530,D531,D532,D533,D534,D535,D536,D537,D538,D539,D540,D541,D542,D543,D544,D545",2020,C965555,WS2812B-2020,180
2A,F1,1812,C20812,SMD1812P200TF16 (PTC 2A hold),1
USB_C,J1,USB-C SMD,C165948,TYPE-C-31-M-12,1
S2B-PH-SM4-TB,"J101,J102",JST PH 2P SMD,C295747,S2B-PH-SM4-TB(LF)(SN),2
MMBT3904,"Q1,Q2",SOT-23,C20526,MMBT3904,2
2N7002,Q3,SOT-23,C8545,2N7002,1
5.1k,"R1,R2",0603,C23186,0603WAF5101T5E,2
10k,"R3,R4,R5,R6,R7,R16,R17,R18",0603,C25804,0603WAF1002T5E,8
470,"R8,R13,R14,R15",0603,C23179,0603WAF4700T5E,4
100k,R9,0603,C25803,0603WAF1003T5E,1
33,"R10,R11,R12",0603,C23140,0603WAF330JT5E,3
1M,"R101,R102",0603,C22935,0603WAF1004T5E,2
AP2112K-3.3,U1,SOT-23-5,C51118,AP2112K-3.3TRG1,1
USBLC6-2SC6,U2,SOT-23-6,C7519,USBLC6-2SC6,1
ESP32-WROOM-32E,U3,Module,C701341,ESP32-WROOM-32E-N4,1
CH340C,U5,SOIC-16,C84681,CH340C,1
74AHCT125,U6,SOIC-14,C554502,"74AHCT125D,118",1
MAX98357A,"U101,U102",TQFN-16 3x3,C910544,MAX98357AETE+T,2
